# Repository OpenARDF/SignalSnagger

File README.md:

# SignalSnagger
<b>Project Status</b>

SignalSnagger is still in development. Product design and BOM contents are preliminary and incomplete.

<b>Concept</b>

SignalSnagger is an 80-meter band radio orienteering (ARDF) direction-finding receiver designed to operate in the Amateur Radio Service 3.5 MHz to 3.7 MHz frequency range. The receiver is designed to perform well in all common radio orienteering event formats: classic, sprint, and foxoring. SignalSnagger's frequency is stable and accurate using a precision temperature-compensated signal generator. A tuned loop with a "sense antenna," based on Dale Hunt's WB6BYU proven design, provides reliable signal-direction readings over a wide range of signal levels. This is an affordable, modern, competition-grade receiver design.

<b>Mechanical Design</b>

The mechanical design is optimized for simplicity, ruggedness, and ergonomic comfort. Left/right symmetry makes the receiver equally usable for left and right handers. Only the front knob (attached to a rotary encoder) extends beyond the walls of the chassis box, helping to minimize the risk of damage during transport or if dropped. Aside from the wires running to the battery, there is no point-to-point wiring - all connections are handled by PCB traces and parts mounted to the circuit board, eliminating unreliable point-to-point wiring. The headphone jack is on the bottom of the receiver, preventing water intrusion. The square antenna geometry makes for a stronger loop that can be readily fabricated using 3D printing. Switches for sense and configuration are recessed and immune to water penetration. The battery can be charged or replaced without opening the receiver chassis. If something breaks or wears out, all parts are readily available from online vendors, and the schematic diagram and BOM are provided, facilitating customer troubleshooting and repair.

<b>Electronics Design</b>

The electronics design is optimized to avoid part obsolescence and to provide high performance. SignalSnagger uses a Software Defined Radio design, utilizing a quadrature sampling detector to provide high dynamic range and to maximize software-upgradable features. A 25-MHz processor capable of sampling the baseband signal can filter and process the audio to achieve reliable signal strength indication and signal detection and supports DSP algorithms to achieve unparalleled SNR performance to detect weak signals deep in the noise.

<b>Free and Open Design</b>

The SignalSnagger project is 100% Open Source. All software and hardware design documents can be downloaded from this GitHub repository.

BOM: https://docs.google.com/spreadsheets/d/1Z3T1SeX6hfT8fjVtJgXu2S2YWHPFD_kywdSzAihOS8g/edit?usp=sharing

Also, check out SignalSnagger's sibling transmitter project: <a href="https://github.com/OpenARDF/SignalSlinger">SignalSlinger</a>.

## Firmware development

Firmware source lives in
[`Software/AVR128DA48/SignalSnagger`](Software/AVR128DA48/SignalSnagger).
Development and release work follows the same core OpenARDF policy used by
SignalSlinger, adapted for SignalSnagger's single AVR128DA48 target:

- [Codex workflow](CODEX_WORKFLOW.md)
- [Build environment](BUILD_ENVIRONMENT.md)
- [Firmware safety invariants](FIRMWARE_SAFETY.md)
- [Feature roadmap](Docs/feature-roadmap.md)
- [Release workflow](RELEASE_WORKFLOW.md)

Start repository work with `just --list`. Use `just check` for the complete
local change gate and `just release-preflight` for deterministic
release-candidate and package verification. `just release-package` creates the
single-target GitHub deliverables: a standalone AVR128DA48 firmware HEX and a
matching release ZIP with metadata, checksums, and programming guidance. The
Si5351 quadrature strategy is experimentally established and must not be
changed without focused regression tests and representative hardware
measurements.

Firmware and software topics integrate through `Development1`; KiCad and
receiver-simulation topics integrate separately through `Development1-KiCad`.
Each collector is promoted to `main` with its own cumulative pull request. Use
`just branch-route-check <collector>` before topic work and `just
collector-preflight <collector>` before promotion. `main` remains linear;
collector pull requests use merge commits so topic and synchronized `main`
ancestry are preserved. After a promotion, use `just collector-sync-check
<collector>` on each focused synchronization topic before merging it.

Every GitHub release follows the mandatory ordered process in
[RELEASE_WORKFLOW.md](RELEASE_WORKFLOW.md), including a reviewed release commit,
clean deterministic packaging, an immutable annotated tag, exact two-asset
publication, fresh-download verification, and checked post-tag evidence.

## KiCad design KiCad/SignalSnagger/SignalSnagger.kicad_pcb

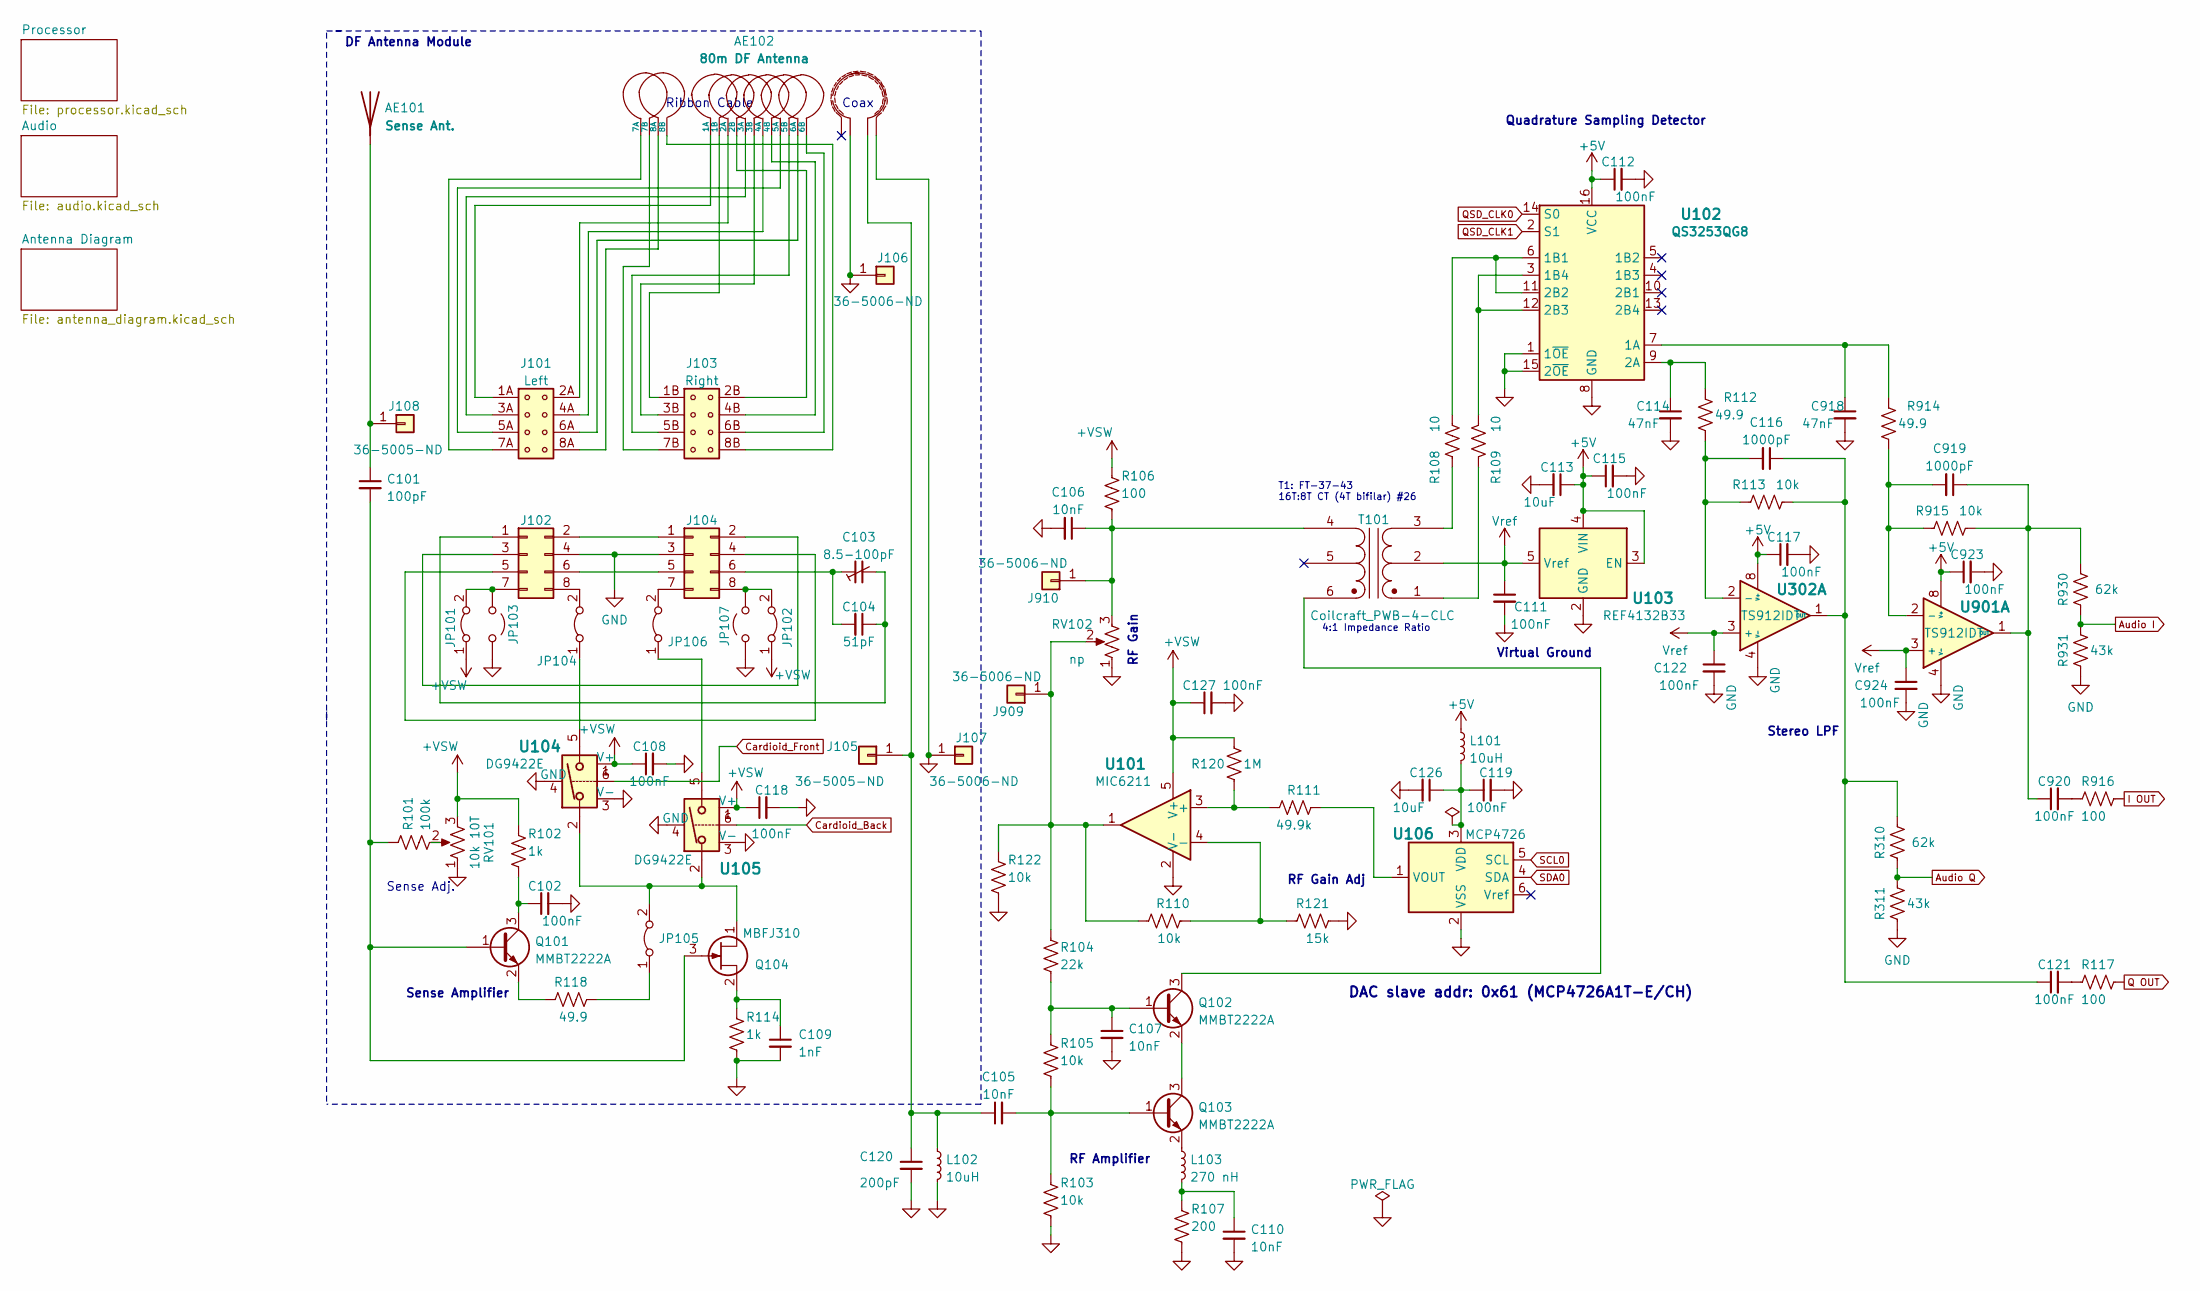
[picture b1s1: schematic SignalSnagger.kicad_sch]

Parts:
AE101: Sense Ant.; Dummy_Empty
AE102: 80m DF Antenna; Dummy_Empty
C101: 100pF; C_0603_1608Metric; Manufacturer PN CC0603JRNPO9BN101; Digi-Key Part No. 311-1069-1-ND
C102, C108, C111, C112, C115, C117, C118, C119, C121, C122, C127, C920, C923, C924: 100nF; C_0603_1608Metric; Manufacturer PN CL10B104KA8NNNC; Digi-Key Part No. 1276-1006-1-ND
C103: 8.5-100pF; VC07B; Manufacturer PN CTC07RB-100; Digi-Key Part No. N/P
C104: 51pF; C_0603_1608Metric; Manufacturer PN CL10C510JB8NNNC; Digi-Key Part No. 1276-2310-1-ND
C105, C106, C107, C110: 10nF; C_0603_1608Metric; Manufacturer PN GRM1885C1H103JA01D; Digi-Key Part No. 490-9666-1-ND
C109: 1nF; C_0603_1608Metric; Manufacturer PN CC0603JRNPO9BN101; Digi-Key Part No. 311-1069-1-ND
C113, C126: 10uF; C_0603_1608Metric; Manufacturer PN GRM188C81C106MA73D; Digi-Key Part No. 490-7198-1-ND
C114, C918: 47nF; C_0603_1608Metric; Manufacturer PN C0603X473J4RECAUTO7411; Digi-Key Part No. 399-C0603X473J4RECAUTO7411CT-ND
C116, C919: 1000pF; C_0603_1608Metric; Manufacturer PN CL10C102JB8NNNC; Digi-Key Part No. 1276-1091-1-ND
C120: 200pF; C_0603_1608Metric; Manufacturer PN CL10C201JB8NNNC; Digi-Key Part No. 399-C0603X103J4HACAUTOCT-ND
J101: Left; Dummy_Empty
J102, J104: 69830-008LF; Manufacturer PN 69830-008LF; Digi-Key Part No. 609-3083-ND
J103: Right; Dummy_Empty
J105, J108: 36-5005-ND; Pin_D1.6mm_L8.5mm_W2.8mm_FlatFork; Digi-Key Part No. N/P
J106, J107, J909, J910: 36-5006-ND; Pin_D1.6mm_L8.5mm_W2.8mm_FlatFork; Digi-Key Part No. N/P
JP101, JP102, JP104, JP105, JP106: Jumper_2_Bridged; Jumper_THT-1x02_Bridged_Circular; Digi-Key Part No. N/P
JP103, JP107: Jumper_2_Open
L101, L102: 10uH; L_0603_1608Metric; Manufacturer PN LBMF1608T100K; Digi-Key Part No. 587-1714-1-ND
L103: 270 nH; L_0603_1608Metric; Manufacturer PN MLF1608DR27JT000; Digi-Key Part No. 445-MLF1608DR27JT000CT-ND
Q101, Q102, Q103: MMBT2222A; SOT-23; Manufacturer PN SMMBT2222ALT1G; Digi-Key Part No. SMMBT2222ALT1GOSCT-ND
Q104: MBFJ310; SOT-23
R101: 100k; R_0603_1608Metric; Manufacturer PN RC0603FR-07100KL; Digi-Key Part No. 311-100KHRCT-ND
R102, R114: 1k; R_0603_1608Metric; Manufacturer PN RC0603FR-071KL; Digi-Key Part No. 311-1.00KHRCT-ND
R103, R105, R110, R113, R122, R915: 10k; R_0603_1608Metric; Manufacturer PN RC0603FR-0710KL; Digi-Key Part No. 311-10.0KHRCT-ND
R104: 22k; R_0603_1608Metric; Manufacturer PN RC0603FR-0722KL; Digi-Key Part No. 311-22.0KHRCT-ND
R106, R117, R916: 100; R_0603_1608Metric; Manufacturer PN RC0603FR-07100RL; Digi-Key Part No. 311-100HRCT-ND
R107: 200; R_0603_1608Metric; Manufacturer PN RC0603FR-13200RL; Digi-Key Part No. 13-RC0603FR-13200RLCT-ND
R108, R109: 10; R_0603_1608Metric; Manufacturer PN RC0603FR-0710RL; Digi-Key Part No. 311-10.0HRCT-ND
R111: 49.9k; R_0603_1608Metric; Manufacturer PN AC0603FR-0749K9L; Digi-Key Part No. 311-49.9KLDCT-ND
R112, R118, R914: 49.9; R_0603_1608Metric; Manufacturer PN ERJ-3EKF49R9V; Digi-Key Part No. P49.9HCT-ND
R120: 1M; R_0603_1608Metric; Manufacturer PN RC0603FR-071ML; Digi-Key Part No. 311-1.00MHRCT-ND
R121: 15k; R_0603_1608Metric; Manufacturer PN RC0603FR-0715KL; Digi-Key Part No. 311-15.0KHRCT-ND
R310, R930: 62k; R_0603_1608Metric; Manufacturer PN RC0603FR-0762KL; Digi-Key Part No. 311-62.0KHRCT-ND
R311, R931: 43k; R_0603_1608Metric; Manufacturer PN RC0603JR-0743KL; Digi-Key Part No. 311-43KGRCT-ND
RV101: 10k 10T; Potentiometer_Bourns_3362P_Vertical; Manufacturer PN 3362P-1-103LF; Digi-Key Part No. 3362P-103LF-ND
RV102: np; PinHeader_1x03_P1.27mm_Vertical
T101: Coilcraft_PWB-4-CLC; Coilcraft-PWB-4-CLC
U101: MIC6211; SOT-23-5; Manufacturer PN MIC6211YM5-TR; Digi-Key Part No. 576-1314-1-ND
U102: QS3253QG8; SSOP-16_4.4x5.2mm_P0.65mm; Manufacturer PN PI5C3253QEX; Digi-Key Part No. PI5C3253QEXDICT-ND
U103: REF4132B33; SOT-23-5; Manufacturer PN REF4132B25DBVR; Digi-Key Part No. 296-REF4132B25DBVRCT-ND
U104, U105: DG9422E; TSOP-6_1.65x3.05mm_P0.95mm; Manufacturer PN DG9422EDV-T1-GE3; Digi-Key Part No. DG9422EDV-T1-GE3CT-ND
U106: MCP4726; SOT-23-6; Manufacturer PN MCP4726A2T-E/CH; Digi-Key Part No. MCP4726A2T-E/CHCT-ND
U302, U901: TS912IDT; SO-8_3.9x4.9mm_P1.27mm; Manufacturer PN TS912IDT; Digi-Key Part No. 497-6618-1-ND

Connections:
+5V: C112.1, C113.1, C115.1, C117.1, C923.1, L101.1, U102.16 (VCC), U103.3 (EN), U103.4 (VIN), U302.8 (V+), U901.8 (V+); also elsewhere on the board
+VSW: C108.1, C118.1, C127.1, JP101.1 (A), JP102.1 (A), R102.1, R106.1, R120.1, RV101.3, U101.5 (V+), U104.1 (V+), U105.1 (V+); also elsewhere on the board
Audio I: R930.2, R931.1; also elsewhere on the board
Audio Q: R310.2, R311.1; also elsewhere on the board
Cardioid_Back: U105.6; also elsewhere on the board
Cardioid_Front: U104.6; also elsewhere on the board
GND: AE102.18, AE102.20, C102.2, C106.2, C107.2, C108.2, C109.2, C110.2, C111.2, C112.2, C113.2, C114.2, C115.2, C117.2, C118.2, C119.2, C120.2, C122.2, C126.2, C127.2, C918.2, C923.2, C924.2, J102.4, J104.3, J106.1, J107.1, JP103.1 (A), JP107.1 (A), L102.2, R103.2, R107.2, R114.2, R121.2, R122.2, R311.2, R931.2, RV101.1, RV102.1, U101.2 (V-), U102.1 (1~OE), U102.8 (GND), U102.15 (2~OE), U103.2 (GND), U104.3 (V-), U104.4 (GND), U105.3 (V-), U105.4 (GND), U106.2 (VSS), U302.4 (V-), U901.4 (V-); also elsewhere on the board
I OUT: R916.2; also elsewhere on the board
unnamed: AE101.1, C101.1, J108.1
unnamed: AE102.1 (7A), J101.7A (Pin_7)
unnamed: AE102.2 (7B), J103.7B (Pin_7)
unnamed: AE102.3 (8A), J101.8A (Pin_8)
unnamed: AE102.4 (8B), J103.8B (Pin_8)
unnamed: AE102.5 (1A), J101.1A (Pin_1)
unnamed: AE102.6 (1B), J103.1B (Pin_1)
unnamed: AE102.7 (2A), J101.2A (Pin_2)
unnamed: AE102.8 (2B), J103.2B (Pin_2)
unnamed: AE102.9 (3A), J101.3A (Pin_3)
unnamed: AE102.10 (3B), J103.3B (Pin_3)
unnamed: AE102.11 (4A), J101.4A (Pin_4)
unnamed: AE102.12 (4B), J103.4B (Pin_4)
unnamed: AE102.13 (5A), J101.5A (Pin_5)
unnamed: AE102.14 (5B), J103.5B (Pin_5)
unnamed: AE102.15 (6A), J101.6A (Pin_6)
unnamed: AE102.16 (6B), J103.6B (Pin_6)
unnamed: C110.1, L103.2, R107.1
unnamed: C121.2, R117.1
unnamed: C920.2, R916.1
unnamed: C103.2, C104.1, J102.1
unnamed: J102.2, J104.1
unnamed: J102.3, J104.2
unnamed: J102.5, J104.4
unnamed: J102.6, J104.5
unnamed: J102.7, JP101.2 (B), JP103.2 (B)
unnamed: J102.8, JP104.2 (B)
unnamed: C103.1, C104.2, J104.6
unnamed: J104.7, JP106.2 (B)
unnamed: J104.8, JP102.2 (B), JP107.2 (B)
unnamed: AE102.19, C105.1, C120.1, J105.1, L102.1
unnamed: J909.1, R104.1, R110.1, R122.1, RV102.2, U101.1
unnamed 89: C106.1, J910.1, R106.2, RV102.3, T101.4 (SB); also elsewhere on the board
unnamed: JP104.1 (A), U104.5
unnamed: JP105.1 (A), R118.1
unnamed: JP105.2 (B), Q104.1 (S), U104.2, U105.2
unnamed: JP106.1 (A), U105.5
unnamed: C101.2, Q101.1 (B), Q104.3 (G), R101.1
unnamed: C102.1, Q101.3 (C), R102.2
unnamed: Q101.2 (E), R118.2
unnamed: C107.1, Q102.1 (B), R104.2, R105.1
unnamed: Q102.3 (C), T101.6 (SA)
unnamed: Q102.2 (E), Q103.3 (C)
unnamed: C105.2, Q103.1 (B), R103.1, R105.2
unnamed: L103.1, Q103.2 (E)
unnamed: C109.1, Q104.2 (D), R114.1
unnamed: R101.2, RV101.2
unnamed: R109.2, T101.1 (PA)
unnamed: R108.2, T101.3 (PB)
unnamed: R111.1, R120.2, U101.3 (+)
unnamed: R110.2, R121.1, U101.4 (-)
unnamed: C918.1, R914.2, U102.7 (1A)
unnamed: R108.1, U102.6 (1B1), U102.11 (2B2)
unnamed: R109.1, U102.3 (1B4), U102.12 (2B3)
unnamed: C114.1, R112.2, U102.9 (2A)
unnamed: C119.1, C126.1, L101.2, U106.3 (VDD)
unnamed: R111.2, U106.1 (VOUT)
unnamed: C116.2, R112.1, R113.2, U302.2 (-)
unnamed: C116.1, C121.1, R113.1, R310.1, U302.1 (OUT)
unnamed: C919.2, R914.1, R915.2, U901.2 (-)
unnamed: C919.1, C920.1, R915.1, R930.1, U901.1 (OUT)
Q OUT: R117.2; also elsewhere on the board
QSD_CLK0: U102.14 (S0); also elsewhere on the board
QSD_CLK1: U102.2 (S1); also elsewhere on the board
SCL0: U106.5 (SCL); also elsewhere on the board
SDA0: U106.4 (SDA); also elsewhere on the board
Vref: C111.1, C122.1, C924.1, T101.2 (P_CT), U103.5 (Vref), U302.3 (+), U901.3 (+); also elsewhere on the board

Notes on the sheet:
DF Antenna Module
RF Gain
Stereo LPF
Sense Amplifier
DAC slave addr: 0x61 (MCP4726A1T-E/CH)
RF Gain Adj
Coax
RF Amplifier
Quadrature Sampling Detector
Virtual Ground
T1: FT-37-43 16T:8T CT (4T bifilar) #26
4:1 Impedance Ratio
Ribbon Cable
Sense Adj.

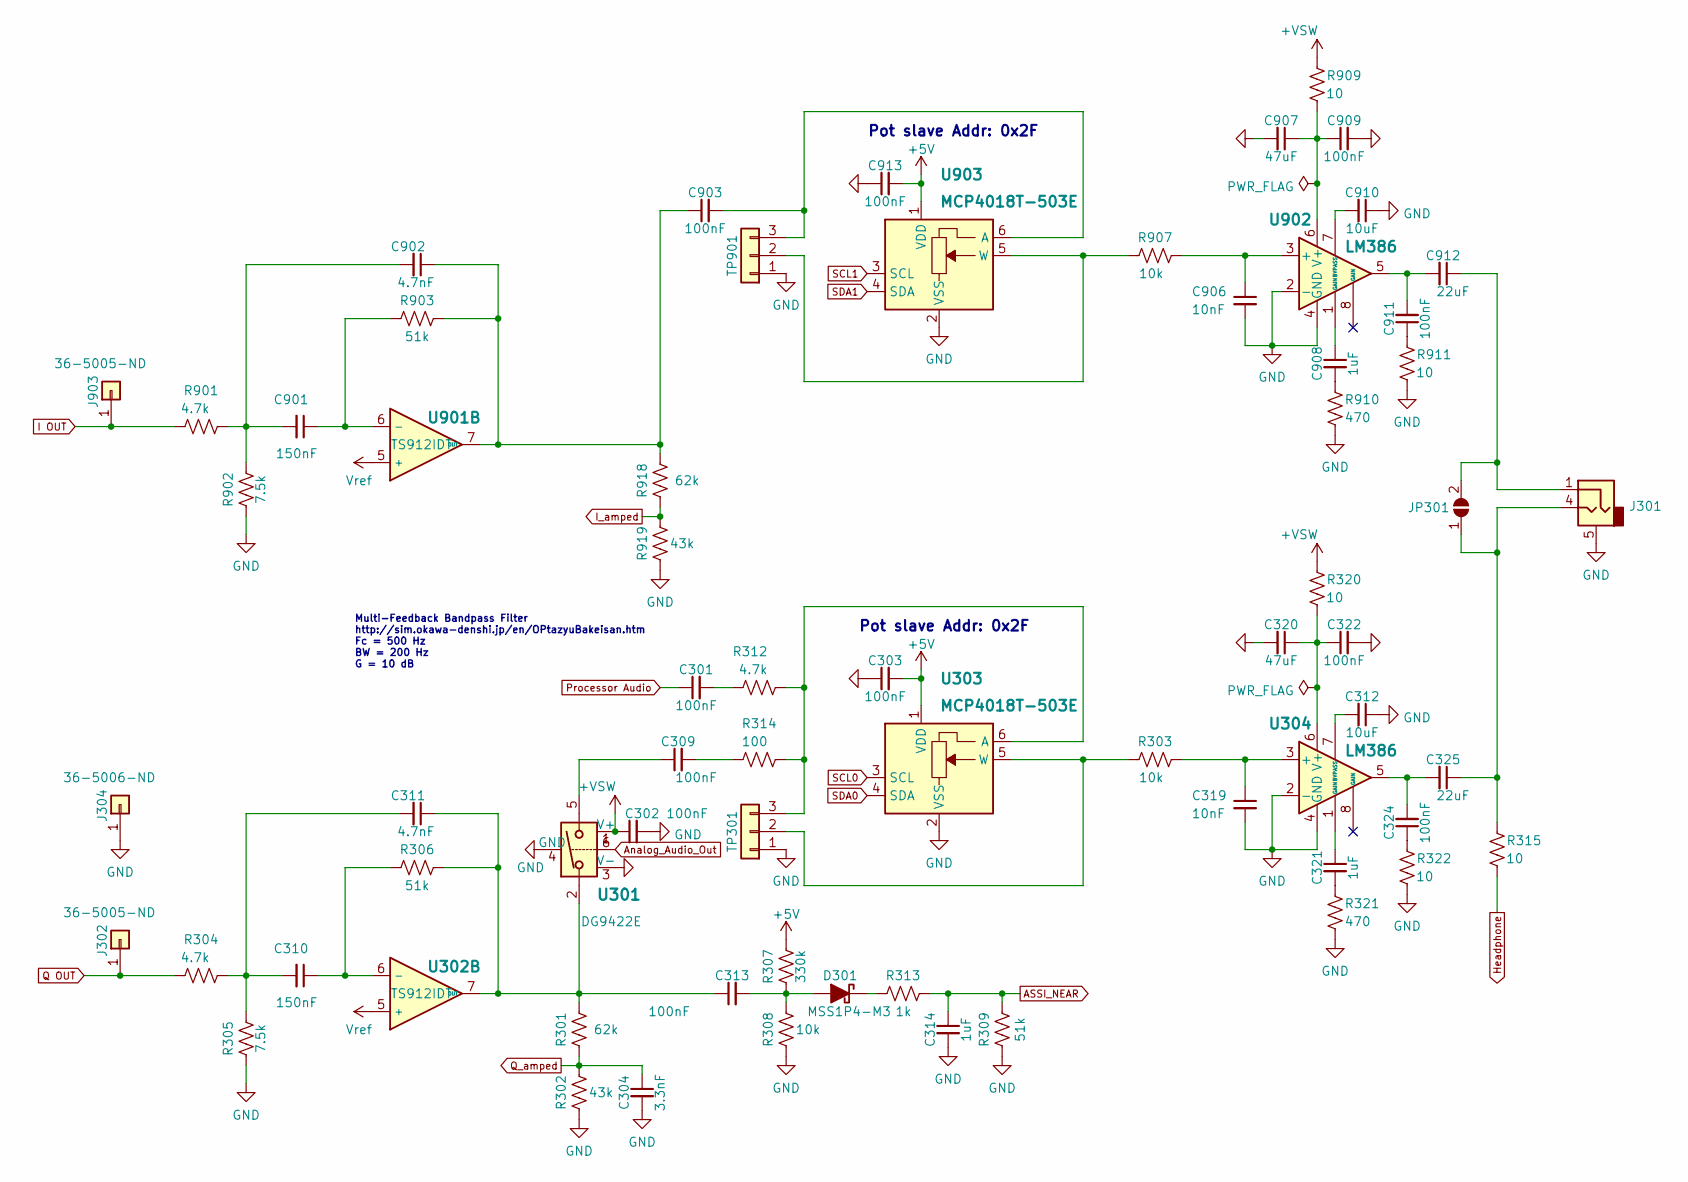
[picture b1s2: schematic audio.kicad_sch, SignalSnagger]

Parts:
C301, C302, C303, C309, C313, C322, C324, C903, C909, C911, C913: 100nF; C_0603_1608Metric; Manufacturer PN CL10B104KA8NNNC; Digi-Key Part No. 1276-1006-1-ND
C304: 3.3nF; C_0603_1608Metric; Manufacturer PN C0603C332J3GAC7867; Digi-Key Part No. 399-15394-1-ND
C310, C901: 150nF; C_0603_1608Metric; Manufacturer PN C0603C154J4RAC7867; Digi-Key Part No. 399-C0603C154J4RAC7867CT-ND
C311, C902: 4.7nF; C_0603_1608Metric; Manufacturer PN C0603C472K4RECAUTO; Digi-Key Part No. 399-17879-1-ND
C312, C910: 10uF; C_0603_1608Metric; Manufacturer PN GRM188C81C106MA73D; Digi-Key Part No. 490-7198-1-ND
C314, C321, C908: 1uF; C_0603_1608Metric; Manufacturer PN CC0603KRX5R8BB105; Digi-Key Part No. 311-1445-1-ND
C319, C906: 10nF; C_0603_1608Metric; Manufacturer PN GRM1885C1H103JA01D; Digi-Key Part No. 490-9666-1-ND
C320, C907: 47uF; C_1210_3225Metric; Manufacturer PN CL32A476KOJNNNE; Digi-Key Part No. 1276-3376-1-ND
C325, C912: 22uF; C_0805_2012Metric; Manufacturer PN CL21A226MOQNNNE; Digi-Key Part No. 1276-2909-1-ND
D301: MSS1P4-M3; DO-219AD; Manufacturer PN MSS1P4-M3/89A; Digi-Key Part No. MSS1P4-M3/89AGICT-ND
J301: 35RASMT2BHSNTRX; SWITCHCRAFT_35RASMT2BHSNTRX; Manufacturer PN 35RASMT2BHSNTRX; Digi-Key Part No. 137-35RASMT2BHSNTRXCT-ND
J302, J903: 36-5005-ND; Pin_D1.6mm_L8.5mm_W2.8mm_FlatFork; Digi-Key Part No. N/P
J304: 36-5006-ND; Pin_D1.6mm_L8.5mm_W2.8mm_FlatFork; Digi-Key Part No. N/P
JP301: SolderJumper_2_Open; SolderJumper-2_P1.3mm_Open_RoundedPad1.0x1.5mm; Digi-Key Part No. N/P
R301, R918: 62k; R_0603_1608Metric; Manufacturer PN RC0603FR-0762KL; Digi-Key Part No. 311-62.0KHRCT-ND
R302, R919: 43k; R_0603_1608Metric; Manufacturer PN RC0603JR-0743KL; Digi-Key Part No. 311-43KGRCT-ND
R303, R308, R907: 10k; R_0603_1608Metric; Manufacturer PN RC0603FR-0710KL; Digi-Key Part No. 311-10.0KHRCT-ND
R304, R312, R901: 4.7k; R_0603_1608Metric; Manufacturer PN RC0603FR-074K7L; Digi-Key Part No. 311-4.70KHRCT-ND
R305, R902: 7.5k; R_0603_1608Metric; Manufacturer PN RC0603FR-077K5L; Digi-Key Part No. 311-7.50KHRCT-ND
R306, R309, R903: 51k; R_0603_1608Metric; Manufacturer PN RC0603FR-0751KL; Digi-Key Part No. 311-51.0KHRCT-ND
R307: 330k; R_0603_1608Metric; Manufacturer PN RC0603FR-07330KL; Digi-Key Part No. 311-330KHRCT-ND
R313: 1k; R_0603_1608Metric; Manufacturer PN RC0603FR-071KL; Digi-Key Part No. 311-1.00KHRCT-ND
R314: 100; R_0603_1608Metric; Manufacturer PN RC0603FR-07100RL; Digi-Key Part No. 311-100HRCT-ND
R315, R322, R911: 10; R_0603_1608Metric; Manufacturer PN RC0603FR-0710RL; Digi-Key Part No. 311-10.0HRCT-ND
R320, R909: 10; R_0805_2012Metric; Manufacturer PN ESR10EZPJ100; Digi-Key Part No. RHM10KCT-ND
R321, R910: 470; R_0603_1608Metric; Manufacturer PN RC0603FR-07470RL; Digi-Key Part No. 311-470HRCT-ND
TP301, TP901: Conn_01x03; PinHeader_1x03_P1.27mm_Vertical; Digi-Key Part No. N/P
U301: DG9422E; TSOP-6_1.65x3.05mm_P0.95mm; Manufacturer PN DG9422EDV-T1-GE3; Digi-Key Part No. DG9422EDV-T1-GE3CT-ND
U302, U901: TS912IDT; SO-8_3.9x4.9mm_P1.27mm; Manufacturer PN TS912IDT; Digi-Key Part No. 497-6618-1-ND
U303, U903: MCP4018T-503E; SOT-363_SC-70-6B; Manufacturer PN MCP4018T-503E/LT; Digi-Key Part No. MCP4018T-503E/LTCT-ND
U304, U902: LM386; SO-8_3.9x4.9mm_P1.27mm; Manufacturer PN LM386MX-1/NOPB; Digi-Key Part No. LM386MX-1/NOPBCT-ND

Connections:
+5V: C303.2, C913.2, R307.1, U303.1 (VDD), U903.1 (VDD); also elsewhere on the board
+VSW: C302.1, R320.1, R909.1, U301.1 (V+); also elsewhere on the board
ASSI_NEAR: C314.1, R309.2, R313.2; also elsewhere on the board
Analog_Audio_Out: U301.6; also elsewhere on the board
GND: C302.2, C303.1, C304.2, C312.1, C314.2, C319.2, C320.2, C322.2, C906.2, C907.2, C909.2, C910.1, C913.1, J301.5, J304.1, R302.2, R305.2, R308.2, R309.1, R321.2, R322.2, R902.2, R910.2, R911.2, R919.2, TP301.1, TP901.1, U301.3 (V-), U301.4 (GND), U303.2 (VSS), U304.2 (-), U304.4 (GND), U902.2 (-), U902.4 (GND), U903.2 (VSS); also elsewhere on the board
Headphone: R315.2; also elsewhere on the board
I OUT: J903.1, R901.1; also elsewhere on the board
I_amped: R918.2, R919.1; also elsewhere on the board
unnamed: C301.2, R312.1
unnamed: C309.1, U301.5
unnamed: C309.2, R314.2
unnamed: C310.2, C311.2, R304.2, R305.1
unnamed: C321.1, U304.1 (GAIN)
unnamed: C321.2, R321.1
unnamed: C324.1, R322.1
unnamed: C324.2, C325.2, U304.5
unnamed: C901.2, C902.2, R901.2, R902.1
unnamed: C908.1, U902.1 (GAIN)
unnamed: C908.2, R910.1
unnamed: C911.1, R911.1
unnamed: C911.2, C912.2, U902.5
unnamed: C313.2, D301.2 (A), R307.2, R308.1
unnamed: D301.1 (K), R313.1
unnamed: C325.1, J301.4, JP301.1 (A), R315.1
unnamed: C912.1, J301.1, JP301.2 (B)
unnamed: R303.1, TP301.2, U303.5 (W)
unnamed: R312.2, R314.1, TP301.3, U303.6 (A)
unnamed: R907.1, TP901.2, U903.5 (W)
unnamed: C903.2, TP901.3, U903.6 (A)
unnamed: C310.1, R306.1, U302.6 (-)
unnamed: C311.1, C313.1, R301.1, R306.2, U301.2, U302.7 (OUT)
unnamed: C319.1, R303.2, U304.3 (+)
unnamed: C312.2, U304.7 (BYPASS)
unnamed: C320.1, C322.1, R320.2, U304.6 (V+)
unnamed: C901.1, R903.1, U901.6 (-)
unnamed: C902.1, C903.1, R903.2, R918.1, U901.7 (OUT)
unnamed: C906.1, R907.2, U902.3 (+)
unnamed: C910.2, U902.7 (BYPASS)
unnamed: C907.1, C909.1, R909.2, U902.6 (V+)
Processor Audio: C301.1; also elsewhere on the board
Q OUT: J302.1, R304.1; also elsewhere on the board
Q_amped: C304.1, R301.2, R302.1; also elsewhere on the board
SCL0: U303.3 (SCL); also elsewhere on the board
SCL1: U903.3 (SCL); also elsewhere on the board
SDA0: U303.4 (SDA); also elsewhere on the board
SDA1: U903.4 (SDA); also elsewhere on the board
Vref: U302.5 (+), U901.5 (+); also elsewhere on the board

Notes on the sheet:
Pot slave Addr: 0x2F
Multi-Feedback Bandpass Filter http://sim.okawa-denshi.jp/en/OPtazyuBakeisan.htm Fc = 500 Hz BW = 200 Hz G = 10 dB

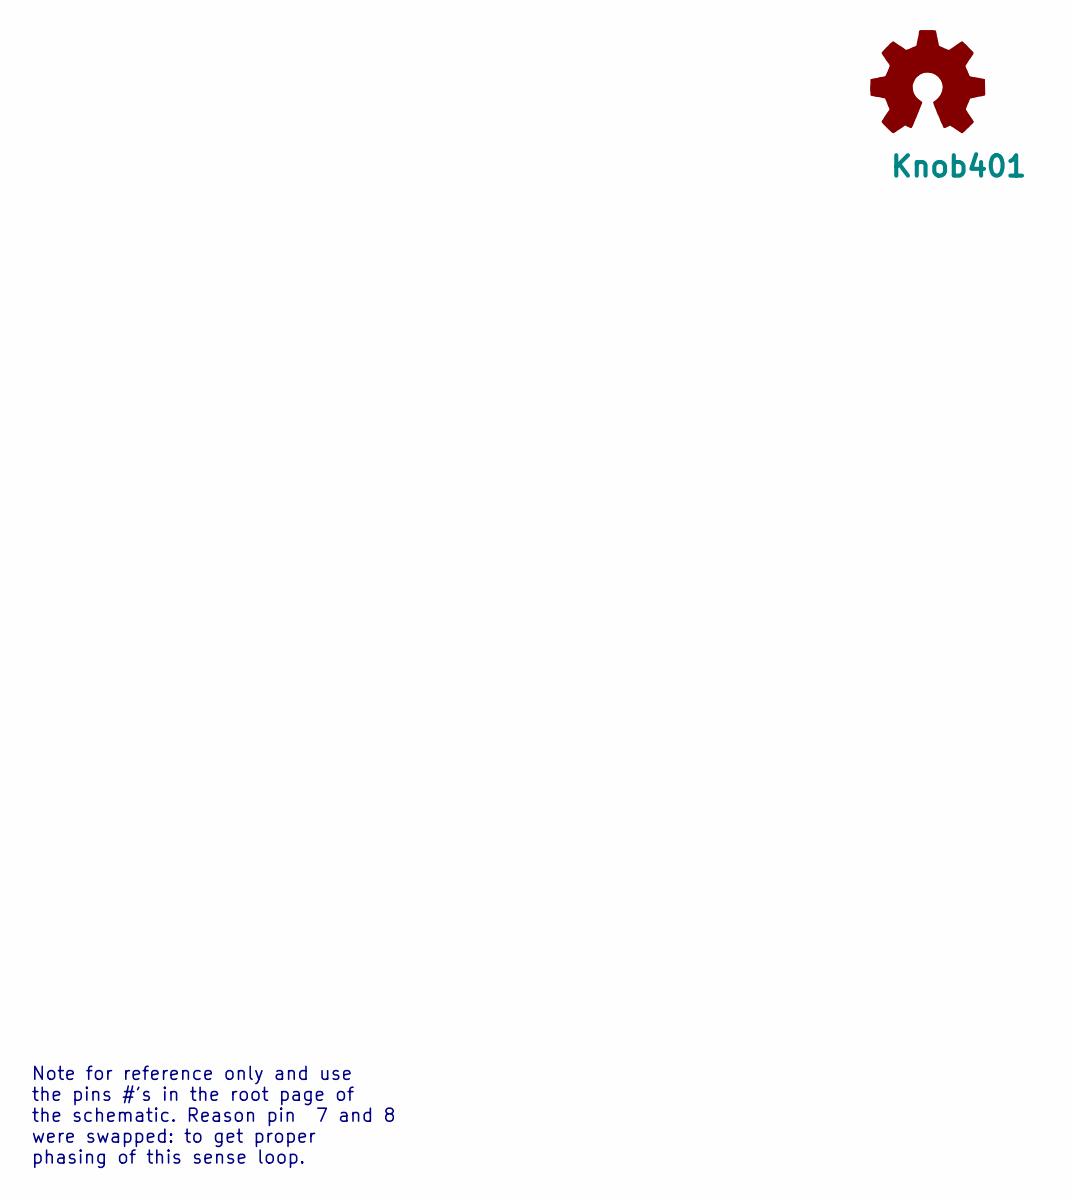
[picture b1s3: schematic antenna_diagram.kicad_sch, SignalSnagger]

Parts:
Knob401: Logo_Open_Hardware_Small; Dummy_Empty

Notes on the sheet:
Note for reference only and use the pins #'s in the root page of the schematic. Reason pin 7 and 8 were swapped: to get proper phasing of this sense loop.
